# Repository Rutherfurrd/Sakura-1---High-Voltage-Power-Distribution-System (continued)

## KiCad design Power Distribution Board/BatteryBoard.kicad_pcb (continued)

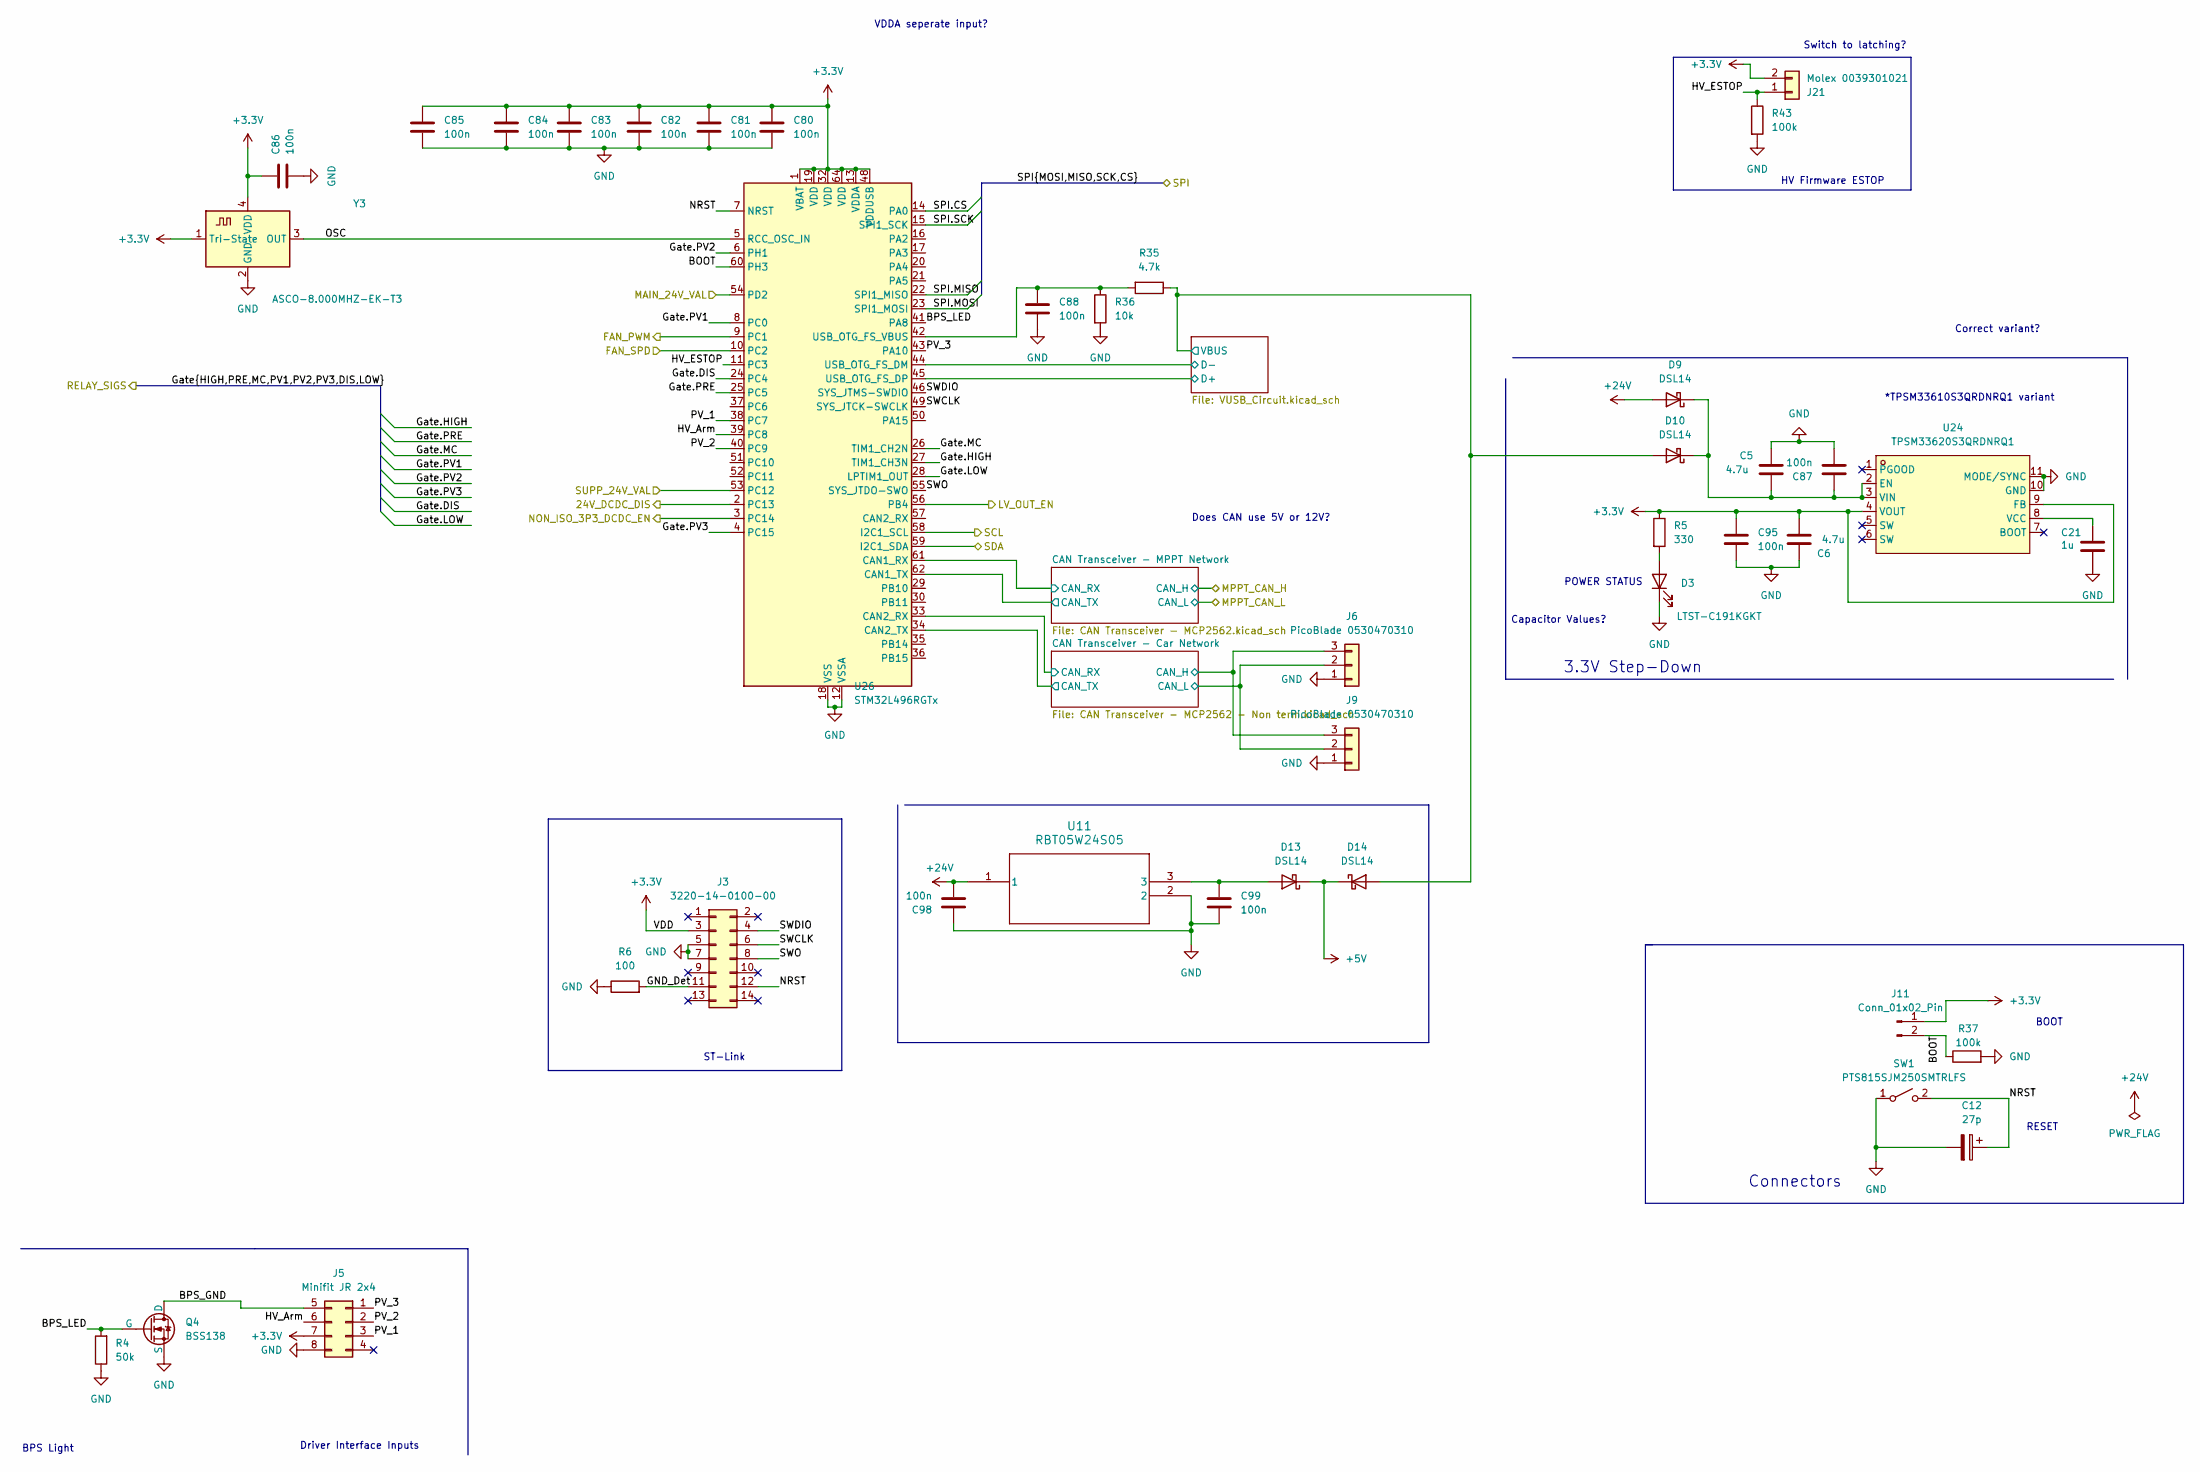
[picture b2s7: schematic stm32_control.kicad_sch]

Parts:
C5, C6: 4.7u; C_0603_1608Metric_Pad1.08x0.95mm_HandSolder; Rating 50V; LCSC C19666
C12: 27p; C_0603_1608Metric_Pad1.08x0.95mm_HandSolder; LCSC C107045
C21: 1u; C_0603_1608Metric_Pad1.08x0.95mm_HandSolder; LCSC C15849
C80, C81, C82, C83, C84, C85, C86, C87, C88, C95, C98, C99: 100n; C_0603_1608Metric_Pad1.08x0.95mm_HandSolder; Rating 50V; LCSC C14663
D3: LTST-C191KGKT; LED_0603_1608Metric_Pad1.05x0.95mm_HandSolder; DigiKey_Part_Number 160-1446-1-ND
D9, D10, D13, D14: DSL14; D_SOD-123FL; LCSC C22466349
J3: 3220-14-0100-00; PinHeader_2x07_P1.27mm_Vertical_SMD; DigiKey_Part_Number SAM13170CT-ND
J5: Minifit JR 2x4; Molex_Mini-Fit_Jr_5566-08A_2x04_P4.20mm_Vertical; DigiKey_Part_Number WM3846-ND
J6, J9: PicoBlade 0530470310; Molex_PicoBlade_53047-0310_1x03_P1.25mm_Vertical; DigiKey_Part_Number WM1732-ND
J11: Conn_01x02_Pin; HARWIN_M20-9990246; DigiKey_Part_Number 952-2262-ND
J21: Molex 0039301021; Molex_Mini-Fit_Jr_5566-02A_2x01_P4.20mm_Vertical; DigiKey_Part_Number WM3843-ND
Q4: BSS138; SOT-23; LCSC C7420339
R4: 50k; R_0603_1608Metric_Pad0.98x0.95mm_HandSolder; LCSC C23184
R5: 330; R_0603_1608Metric_Pad0.98x0.95mm_HandSolder; LCSC C23138
R6: 100; R_0603_1608Metric_Pad0.98x0.95mm_HandSolder; LCSC C22775
R35: 4.7k; R_0603_1608Metric_Pad0.98x0.95mm_HandSolder; LCSC C23162
R36: 10k; R_0603_1608Metric_Pad0.98x0.95mm_HandSolder; LCSC C95204
R37, R43: 100k; R_0603_1608Metric_Pad0.98x0.95mm_HandSolder; LCSC C25803
SW1: PTS815SJM250SMTRLFS; SW_SPST_PTS810; DigiKey_Part_Number CKN12215-2-ND
U11: RBT05W24S05; RBT10W24S05_XPP_XPR; DigiKey_Part_Number 1470-RBT05W24S05-ND
U24: TPSM33620S3QRDNRQ1; QFN-11_L4.5-W3.5-P0.50-TL_TPSM365R6FRDNR; MPN TPSM33620S3QRDNRQ1; LCSC C49261907
U26: STM32L496RGTx; LQFP-64_10x10mm_P0.5mm; LCSC C124720
Y3: ASCO-8.000MHZ-EK-T3; Oscillator_SMD_Abracon_ASCO-4Pin_1.6x1.2mm; DigiKey_Part_Number 535-12077-1-ND

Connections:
+3.3V: C6.1, C80.1, C81.1, C82.1, C83.1, C84.1, C85.1, C86.1, C95.1, J3.3, J5.7, J11.1, J21.2, R5.1, U24.4 (VOUT), U24.9 (FB), U26.1 (VBAT), U26.13 (VDDA), U26.19 (VDD), U26.32 (VDD), U26.48 (VDDUSB), U26.64 (VDD), Y3.1 (Tri-State), Y3.4 (VDD); also elsewhere on the board
+5V: D13.1 (K), D14.1 (K); also elsewhere on the board
+24V: C98.2, D9.2 (A), U11.1; also elsewhere on the board
/24 Supplementary Switch/LV_OUT_EN: U26.56 (PB4); also elsewhere on the board
/24 Supplementary Switch/MAIN_24V_VALID: U26.53 (PC12); also elsewhere on the board
/24 Supplementary Switch/SUPP_24V_VALID: U26.54 (PD2); also elsewhere on the board
/<NO NET>: U26.58 (I2C1_SCL); also elsewhere on the board
/Battery Fan/FAN1_SPD: U26.10 (PC2); also elsewhere on the board
/Battery Fan/FAN_PWM: U26.9 (PC1); also elsewhere on the board
/Gate.DIS: U26.24 (PC4); also elsewhere on the board
/Gate.HIGH: U26.27 (TIM1_CH3N); also elsewhere on the board
/Gate.LOW: U26.28 (LPTIM1_OUT); also elsewhere on the board
/Gate.MC: U26.26 (TIM1_CH2N); also elsewhere on the board
/Gate.PRE: U26.25 (PC5); also elsewhere on the board
/Gate.PV1: U26.8 (PC0); also elsewhere on the board
/Gate.PV2: U26.6 (PH1); also elsewhere on the board
/Gate.PV3: U26.4 (PC15); also elsewhere on the board
/LV Step-down/24V_CONV_EN_ACTIVELOW: U26.2 (PC13); also elsewhere on the board
/LV Step-down/NON_ISO_3P3_EN: U26.3 (PC14); also elsewhere on the board
/SDA: U26.59 (I2C1_SDA); also elsewhere on the board
/SPI.CS: U26.14 (PA0); also elsewhere on the board
/SPI.MISO: U26.22 (SPI1_MISO); also elsewhere on the board
/SPI.MOSI: U26.23 (SPI1_MOSI); also elsewhere on the board
/SPI.SCK: U26.15 (SPI1_SCK); also elsewhere on the board
/STM32_CONTROL/BOOT: J11.2, R37.1, U26.60 (PH3)
/STM32_CONTROL/BPS_GND: J5.5, Q4.1 (D)
/STM32_CONTROL/BPS_LED: Q4.2 (G), R4.2, U26.41 (PA8)
/STM32_CONTROL/CAN Transceiver - Car Network/CAN+: J6.3, J9.3; also elsewhere on the board
/STM32_CONTROL/CAN Transceiver - Car Network/CAN-: J6.2, J9.2; also elsewhere on the board
/STM32_CONTROL/CAN Transceiver - Car Network/CAN_RX: U26.33 (CAN2_RX); also elsewhere on the board
/STM32_CONTROL/CAN Transceiver - Car Network/CAN_TX: U26.34 (CAN2_TX); also elsewhere on the board
/STM32_CONTROL/CAN Transceiver - MPPT Network/CAN_RX: U26.61 (CAN1_RX); also elsewhere on the board
/STM32_CONTROL/CAN Transceiver - MPPT Network/CAN_TX: U26.62 (CAN1_TX); also elsewhere on the board
/STM32_CONTROL/GND_Det: J3.11, R6.2
/STM32_CONTROL/HV_Arm: J5.6, U26.39 (PC8)
/STM32_CONTROL/HV_ESTOP: J21.1, R43.1, U26.11 (PC3)
/STM32_CONTROL/NRST: C12.1, J3.12, SW1.2 (B), U26.7 (NRST)
/STM32_CONTROL/OSC: U26.5 (RCC_OSC_IN), Y3.3 (OUT)
/STM32_CONTROL/PV_1: J5.3, U26.38 (PC7)
/STM32_CONTROL/PV_2: J5.2, U26.40 (PC9)
/STM32_CONTROL/PV_3: J5.1, U26.43 (PA10)
/STM32_CONTROL/SWCLK: J3.6, U26.49 (SYS_JTCK-SWCLK)
/STM32_CONTROL/SWDIO: J3.4, U26.46 (SYS_JTMS-SWDIO)
/STM32_CONTROL/SWO: J3.8, U26.55 (SYS_JTDO-SWO)
/STM32_CONTROL/USC_CIRCUIT/D+: U26.45 (USB_OTG_FS_DP); also elsewhere on the board
/STM32_CONTROL/USC_CIRCUIT/D-: U26.44 (USB_OTG_FS_DM); also elsewhere on the board
/STM32_CONTROL/USC_CIRCUIT/VBUS: D10.2 (A), D14.2 (A), R35.1; also elsewhere on the board
GND: C5.2, C6.2, C12.2, C21.1, C80.2, C81.2, C82.2, C83.2, C84.2, C85.2, C86.2, C87.2, C88.2, C95.2, C98.1, C99.2, D3.1 (K), J3.5, J3.7, J5.8, J6.1, J9.1, Q4.3 (S), R4.1, R6.1, R36.2, R37.2, R43.2, SW1.1 (A), U11.2, U24.10 (GND), U24.11 (MODE/SYNC), U26.12 (VSSA), U26.18 (VSS), U26.31 (VSS), U26.47 (VSS), U26.63 (VSS), Y3.2 (GND); also elsewhere on the board
unnamed: D3.2 (A), R5.2
unnamed: C5.1, C87.1, D9.1 (K), D10.1 (K), U24.2 (EN), U24.3 (VIN)
unnamed: C99.1, D13.2 (A), U11.3
unnamed: C21.2, U24.8 (VCC)
unnamed: C88.1, R35.2, R36.1, U26.42 (USB_OTG_FS_VBUS)

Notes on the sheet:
HV Firmware ESTOP
Does CAN use 5V or 12V?
Capacitor Values?
*TPSM33610S3QRDNRQ1 variant
Driver Interface Inputs
BPS Light
Correct variant?
Connectors
3.3V Step-Down
ST-Link
BOOT
Switch to latching?
RESET
VDDA seperate input?
POWER STATUS

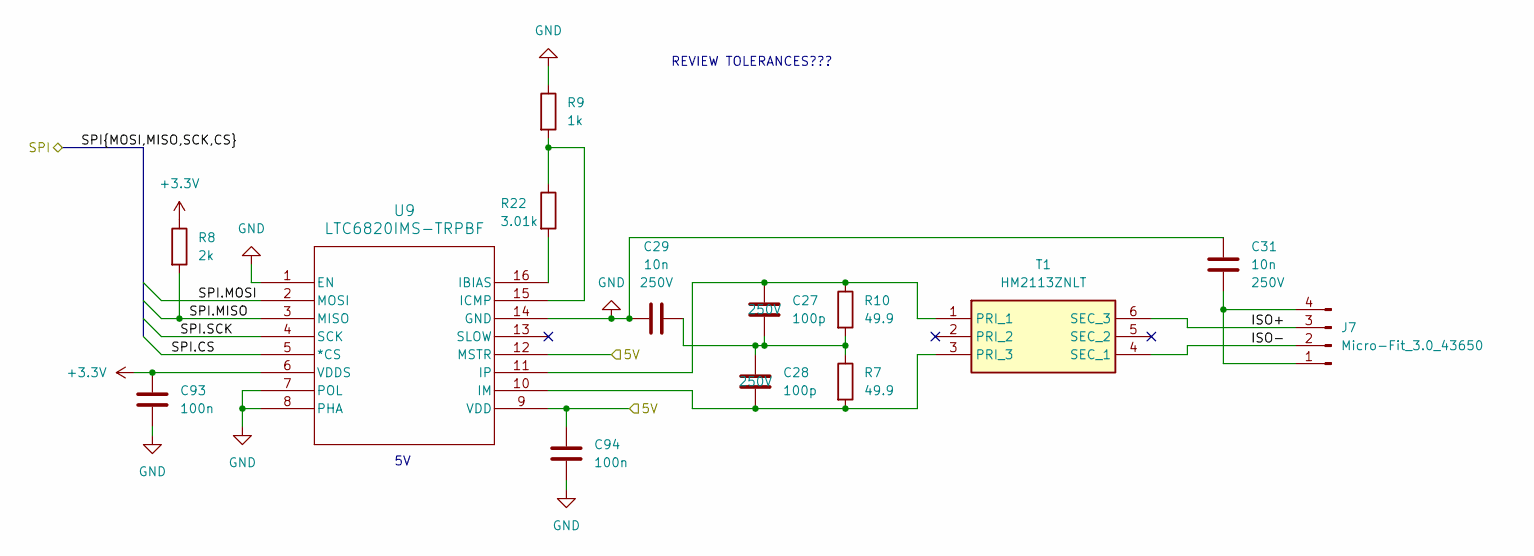
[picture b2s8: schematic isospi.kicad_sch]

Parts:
C27, C28: 100p; C_0603_1608Metric_Pad1.08x0.95mm_HandSolder; LCSC C14858
C29, C31: 10n; C_0603_1608Metric_Pad1.08x0.95mm_HandSolder; LCSC C57112
C93, C94: 100n; C_0603_1608Metric_Pad1.08x0.95mm_HandSolder; Rating 50V; LCSC C14663
J7: Micro-Fit_3.0_43650; Molex_Micro-Fit_3.0_43650-0415_1x04_P3.00mm_Vertical; DigiKey_Part_Number WM1919-ND
R7, R10: 49.9; R_0603_1608Metric_Pad0.98x0.95mm_HandSolder; LCSC C23185
R8: 2k; R_0603_1608Metric_Pad0.98x0.95mm_HandSolder; LCSC C22975
R9: 1k; R_0603_1608Metric_Pad0.98x0.95mm_HandSolder; LCSC C21190
R22: 3.01k; R_0603_1608Metric_Pad0.98x0.95mm_HandSolder; LCSC C22991
T1: HM2113ZNLT; Mouser Part Number 673-HM2113ZNLT
U9: LTC6820IMS-TRPBF; MS_05-08-1669_ADI; LCSC C581009

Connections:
+3.3V: C93.1, R8.1, U9.6 (VDDS); also elsewhere on the board
+5V: C94.1, U9.9 (VDD), U9.12 (MSTR); also elsewhere on the board
/ISOSPI/ISO+: J7.3, T1.6 (SEC_3)
/ISOSPI/ISO-: J7.2, T1.4 (SEC_1)
/SPI.CS: U9.5 (*CS); also elsewhere on the board
/SPI.MISO: R8.2, U9.3 (MISO); also elsewhere on the board
/SPI.MOSI: U9.2 (MOSI); also elsewhere on the board
/SPI.SCK: U9.4 (SCK); also elsewhere on the board
GND: C29.1, C31.2, C93.2, C94.2, R9.1, U9.1 (EN), U9.7 (POL), U9.8 (PHA), U9.14 (GND); also elsewhere on the board
unnamed: C27.2, C28.1, C29.2, R7.1, R10.2
unnamed: C31.1, J7.1, J7.4
unnamed: C27.1, R10.1, T1.1 (PRI_1), U9.11 (IP)
unnamed: C28.2, R7.2, T1.3 (PRI_3), U9.10 (IM)
unnamed: R22.2, U9.16 (IBIAS)
unnamed: R9.2, R22.1, U9.15 (ICMP)

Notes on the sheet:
REVIEW TOLERANCES???

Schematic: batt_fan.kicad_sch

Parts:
C48: 10u; CP_Radial_D10.0mm_P5.00mm; DigiKey_Part_Number 450BXC10MEFC10X20
J8: B4B-PH-K-S; JST_PH_B4B-PH-K_1x04_P2.00mm_Vertical; DigiKey_Part_Number N/A
Q14: BSS138; SOT-23; LCSC C7420339
R19, R41: 2k; R_0603_1608Metric_Pad0.98x0.95mm_HandSolder; LCSC C22975

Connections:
+3.3V: R19.1, R41.1; also elsewhere on the board
+24V: C48.1, J8.3; also elsewhere on the board
/Battery Fan/FAN1_SPD: J8.1, R19.2; also elsewhere on the board
/Battery Fan/FAN_PWM: Q14.1 (G), R41.2; also elsewhere on the board
GND: C48.2, J8.2, Q14.2 (S); also elsewhere on the board
unnamed: J8.4, Q14.3 (D)

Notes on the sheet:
PWR, GND, SENSOR, CNTRL
24 kHz
24VDC, 12W per fan

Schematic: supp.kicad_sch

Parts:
C14: 220u; CP_Radial_D10.0mm_P5.00mm; DigiKey_Part_Number CAP ALUM 220UF 20% 50V RADIAL TH
C38: 1n; C_0603_1608Metric_Pad1.08x0.95mm_HandSolder; LCSC C1588
C64, C65, C75: 10u; C_1206_3216Metric_Pad1.33x1.80mm_HandSolder; LCSC C13585
C74, C76, C77, C78, C79: 100n; C_0603_1608Metric_Pad1.08x0.95mm_HandSolder; Rating 50V; LCSC C14663
D15, D16: SMF30A; D_SMF; LCSC C19077518
J15, J25: Molex 0039301021; Molex_Mini-Fit_Jr_5566-02A_2x01_P4.20mm_Vertical; DigiKey_Part_Number WM3843-ND
K4, K5: G5Q-1A-EU DC24; Relay_SPST_Omron-G5Q-1A; Rating Z5361-ND
Q7, Q8: SI4909DY-T1-GE3; SOIC_09DY-T1-GE3_VIS; LCSC C222523
Q15: BSS138; SOT-23; LCSC C7420339
R26, R27: 100k; R_0603_1608Metric_Pad0.98x0.95mm_HandSolder; LCSC C25803
R28: 15k; R_0603_1608Metric_Pad0.98x0.95mm_HandSolder; LCSC C22809
R32: 2k; R_0603_1608Metric_Pad0.98x0.95mm_HandSolder; LCSC C22975
R45: 120k; R_0603_1608Metric_Pad0.98x0.95mm_HandSolder; LCSC C25808
R46, R61, R62, R63: 2M; R_0603_1608Metric_Pad0.98x0.95mm_HandSolder; LCSC C22976
R47, R64: 75k; R_0603_1608Metric_Pad0.98x0.95mm_HandSolder; LCSC C23242
R49: 255k; R_0805_2012Metric_Pad1.20x1.40mm_HandSolder; LCSC C17578
R51, R53: 20k; R_0603_1608Metric_Pad0.98x0.95mm_HandSolder; LCSC C4184
U3: R-7812-0.5; Converter_DCDC_RECOM_R-78E-0.5_THT; DigiKey_Part_Number 945-1032-ND
U6: LTC4418CUF-TRPBF; UF_20_ADI; LCSC C688512

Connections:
+3.3V: R51.1, R53.1; also elsewhere on the board
+24V: C76.2, K4.3, K5.1, K5.2, U3.1 (IN); also elsewhere on the board
/24 Supplementary Switch/12V_CAN: C74.2, U3.3 (OUT); also elsewhere on the board
/24 Supplementary Switch/24V_MAIN: C64.1, Q7.5 (D2), Q7.6 (D2), R46.1, R61.1, U6.17 (V1); also elsewhere on the board
/24 Supplementary Switch/24V_SUPP: C75.1, Q8.5 (D2), Q8.6 (D2), R62.1, R63.1, U6.16 (V2); also elsewhere on the board
/24 Supplementary Switch/24_OUT: K5.3; also elsewhere on the board
/24 Supplementary Switch/LV_OUT_EN: Q15.1 (G), R27.1; also elsewhere on the board
/24 Supplementary Switch/MAIN_24V_VALID: R51.2, U6.6 (*VALID1); also elsewhere on the board
/24 Supplementary Switch/SUPP_24V_VALID: R53.2, U6.7 (*VALID2); also elsewhere on the board
GND: C14.2, C38.2, C64.2, C65.2, C74.1, C75.2, C76.1, C77.1, C78.1, C79.2, D15.2 (A2), D16.2 (A2), J15.1, J25.1, Q15.2 (S), R27.2, R32.2, R45.2, R47.2, R49.2, R64.2, U3.2 (GND), U6.8 (GND), U6.21 (GND); also elsewhere on the board
unnamed: D15.1 (A1), J15.2, K4.5
unnamed: D16.1 (A1), K5.5, Q15.3 (D)
unnamed: C14.1, C65.1, J25.2, K4.1, K4.2, Q7.7 (D1), Q7.8 (D1), Q8.7 (D1), Q8.8 (D1), U6.15 (VOUT)
unnamed: Q7.2 (G1), Q7.4 (G2), U6.13 (G1)
unnamed: C77.2, Q7.1 (S1), Q7.3 (S2), U6.14 (VS1)
unnamed: Q8.2 (G1), Q8.4 (G2), U6.11 (G2)
unnamed: C78.2, Q8.1 (S1), Q8.3 (S2), U6.12 (VS2)
unnamed: R26.2, R28.1
unnamed: R28.2, R32.1
unnamed: C79.1, U6.10 (INTVCC), U6.18 (EN), U6.19 (*SHDN)
unnamed: R49.1, U6.20 (HYS)
unnamed: R46.2, R47.1, U6.3 (OV1)
unnamed: R62.2, R64.1, U6.5 (OV2)
unnamed: C38.1, U6.1 (TMR)
unnamed: R45.1, R61.2, U6.2 (UV1)
unnamed: R26.1, R63.2, U6.4 (UV2)

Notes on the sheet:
17.5V Min
28V Max
Internal 24V Bus
LV ESTOP
24V Nom
500mV Hys
18.1V Min
Test Power, switching bypass

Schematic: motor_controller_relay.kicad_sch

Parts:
C3: C_Polarized
K3: P126CDA; DigiKey_Part_Number 3596-P126CDA-ND
R3: R

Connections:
+24V: K3.3; also elsewhere on the board
/MC Relay/RELAY_IN: C3.2, K3.2; also elsewhere on the board
/MC Relay/RELAY_OUT: K3.1, R3.1; also elsewhere on the board
/MC Relay/RELAY_PROTECTION_CIRCUIT/COIL_NEG: K3.4; also elsewhere on the board
unnamed: C3.1, R3.2

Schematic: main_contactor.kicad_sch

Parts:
C1: C_Polarized
K1: P126CDA; DigiKey_Part_Number 3596-P126CDA-ND
R1: R

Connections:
+24V: K1.3; also elsewhere on the board
/HV_BUS_POS: K1.1; also elsewhere on the board
/Main Contactor High/RELAY_IN: K1.2; also elsewhere on the board
/Main Contactor High/RELAY_PROTECTION_CIRCUIT/COIL_NEG: K1.4; also elsewhere on the board
unnamed: C1.1, R1.2

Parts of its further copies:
K2: P126CDA; DigiKey_Part_Number 3596-P126CDA-ND

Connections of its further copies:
+24V: K2.3; also elsewhere on the board
-BATT: K2.1; also elsewhere on the board
/Main Contactor Low/RELAY_IN: K2.2; also elsewhere on the board
/Main Contactor Low/RELAY_PROTECTION_CIRCUIT/COIL_NEG: K2.4; also elsewhere on the board

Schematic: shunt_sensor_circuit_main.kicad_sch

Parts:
C39: 10n; C_0603_1608Metric_Pad1.08x0.95mm_HandSolder; Rating 50V; LCSC C57112
C43, C45, C53: 100n; C_0603_1608Metric_Pad1.08x0.95mm_HandSolder; Rating 50V; LCSC C14663
R67: 0.5m; RES-TH_HOFLQ60-100A-50MV-7H27; Rating 200V; LCSC C508587
R78, R79: 100; R_0603_1608Metric_Pad0.98x0.95mm_HandSolder; Rating 75V; LCSC C22775
U42: AMC1302DWVR; DWV0008A; LCSC C2863209
U43: MCP3425A0T-E/CH; SOT-23-6; LCSC C66823

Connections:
+3.3V: C45.1, C53.1, U42.8 (VDD2), U43.5 (V_{DD}); also elsewhere on the board
+3.3VP: C43.2, U42.1 (VDD1); also elsewhere on the board
/<NO NET>: U43.3 (SCL); also elsewhere on the board
/HV_BUS_NEG: C39.2, R67.1, U42.3 (VINN); also elsewhere on the board
/Main Contactor Low/RELAY_IN: C39.1, C43.1, R67.2, U42.2 (VINP), U42.4 (GND1); also elsewhere on the board
/SDA: U43.4 (SDA); also elsewhere on the board
GND: C45.2, C53.2, U42.5 (GND2), U43.2 (V_{SS}); also elsewhere on the board
unnamed: R79.1, U42.6 (VOUTN)
unnamed: R78.1, U42.7 (VOUTP)
unnamed: R79.2, U43.1 (Vin+)
unnamed: R78.2, U43.6 (Vin-)

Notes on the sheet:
Overspec?
40A
*R 10K, 100KHZ. 2K, 400KHZ.
Choose R to fit within bounds of ADC
+- 50 mV

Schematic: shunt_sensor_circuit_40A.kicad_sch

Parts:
C34: 10n; C_0603_1608Metric_Pad1.08x0.95mm_HandSolder; Rating 50V; LCSC C57112
C42, C44, C51: 100n; C_0603_1608Metric_Pad1.08x0.95mm_HandSolder; Rating 50V; LCSC C14663
R48: 0.5m; RES-TH_HOFLQ60-100A-50MV-7H27; Rating 200V; LCSC C508587
R72, R73: 100; R_0603_1608Metric_Pad0.98x0.95mm_HandSolder; Rating 75V; LCSC C22775
U36: AMC1302DWVR; DWV0008A; LCSC C2863209
U37: MCP3425A1T-E/CH; SOT-23-6; LCSC C625479

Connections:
+3.3V: C44.1, C51.1, U36.8 (VDD2), U37.5 (V_{DD}); also elsewhere on the board
+3.3VP: C42.2, U36.1 (VDD1); also elsewhere on the board
/<NO NET>: U37.3 (SCL); also elsewhere on the board
/HV_BUS_NEG: C34.1, C42.1, R48.2, U36.2 (VINP), U36.4 (GND1); also elsewhere on the board
/MC Current Sense/SHUNT_Supply: C34.2, R48.1, U36.3 (VINN); also elsewhere on the board
/SDA: U37.4 (SDA); also elsewhere on the board
GND: C44.2, C51.2, U36.5 (GND2), U37.2 (V_{SS}); also elsewhere on the board
unnamed: R73.1, U36.6 (VOUTN)
unnamed: R72.1, U36.7 (VOUTP)
unnamed: R73.2, U37.1 (Vin+)
unnamed: R72.2, U37.6 (Vin-)

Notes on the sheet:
Overspec?
40A
*R 10K, 100KHZ. 2K, 400KHZ.
Choose R to fit within bounds of ADC
+- 50 mV

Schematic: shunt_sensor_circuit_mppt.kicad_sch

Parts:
C66: 10n; C_0603_1608Metric_Pad1.08x0.95mm_HandSolder; Rating 50V; LCSC C57112
C67, C68, C69: 100n; C_0603_1608Metric_Pad1.08x0.95mm_HandSolder; Rating 50V; LCSC C14663
R50: 0.5m; RES-TH_HOFLQ60-100A-50MV-7H27; Rating 200V; LCSC C508587
R74, R75: 100; R_0603_1608Metric_Pad0.98x0.95mm_HandSolder; Rating 75V; LCSC C22775
U38: AMC1302DWVR; DWV0008A; LCSC C2863209
U39: MCP3425A2T-E/CH; SOT-23-6; LCSC C625480

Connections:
+3.3V: C68.1, C69.1, U38.8 (VDD2), U39.5 (V_{DD}); also elsewhere on the board
+3.3VP: C67.2, U38.1 (VDD1); also elsewhere on the board
/<NO NET>: U39.3 (SCL); also elsewhere on the board
/Elmar Racing MPPTS/HV_BUS_NEG: C66.2, R50.1, U38.3 (VINN); also elsewhere on the board
/HV_BUS_NEG: C66.1, C67.1, R50.2, U38.2 (VINP), U38.4 (GND1); also elsewhere on the board
/SDA: U39.4 (SDA); also elsewhere on the board
GND: C68.2, C69.2, U38.5 (GND2), U39.2 (V_{SS}); also elsewhere on the board
unnamed: R75.1, U38.6 (VOUTN)
unnamed: R74.1, U38.7 (VOUTP)
unnamed: R75.2, U39.1 (Vin+)
unnamed: R74.2, U39.6 (Vin-)

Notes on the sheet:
40A
*R 10K, 100KHZ. 2K, 400KHZ.
+- 50 mV

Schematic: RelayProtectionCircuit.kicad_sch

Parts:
D22: SMF30A; D_SMF; LCSC C19077518
Q1: BSS138; SOT-23; LCSC C7420339
R55: 50k; R_0603_1608Metric_Pad0.98x0.95mm_HandSolder; LCSC C23184

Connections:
/Elmar Racing MPPTS/COIL_RET_1: D22.1 (A1), Q1.3 (D); also elsewhere on the board
/Gate.PV1: Q1.1 (G), R55.1; also elsewhere on the board
GND: D22.2 (A2), Q1.2 (S), R55.2; also elsewhere on the board

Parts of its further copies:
D1, D5, D6, D27, D28, D29, D30: SMF30A; D_SMF; LCSC C19077518
Q2, Q3, Q9, Q10, Q11, Q12, Q13: BSS138; SOT-23; LCSC C7420339
R24, R33, R42, R56, R59, R60, R68: 50k; R_0603_1608Metric_Pad0.98x0.95mm_HandSolder; LCSC C23184

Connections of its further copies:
/Elmar Racing MPPTS/COIL_RET_2: D27.1 (A1), Q2.3 (D); also elsewhere on the board
/Elmar Racing MPPTS/COIL_RET_3: D28.1 (A1), Q3.3 (D); also elsewhere on the board
/Gate.DIS: Q12.1 (G), R68.1; also elsewhere on the board
/Gate.HIGH: Q9.1 (G), R24.1; also elsewhere on the board
/Gate.LOW: Q10.1 (G), R33.1; also elsewhere on the board
/Gate.MC: Q13.1 (G), R42.1; also elsewhere on the board
/Gate.PRE: Q11.1 (G), R60.1; also elsewhere on the board
/Gate.PV2: Q2.1 (G), R56.1; also elsewhere on the board
/Gate.PV3: Q3.1 (G), R59.1; also elsewhere on the board
/MC Relay/RELAY_PROTECTION_CIRCUIT/COIL_NEG: D6.1 (A1), Q13.3 (D); also elsewhere on the board
/Main Contactor High/RELAY_PROTECTION_CIRCUIT/COIL_NEG: D1.1 (A1), Q9.3 (D); also elsewhere on the board
/Main Contactor Low/RELAY_PROTECTION_CIRCUIT/COIL_NEG: D5.1 (A1), Q10.3 (D); also elsewhere on the board
/Pre & Dis Charge/RELAY_PROTECTION_CIRCUIT1/COIL_NEG: D30.1 (A1), Q12.3 (D); also elsewhere on the board
/Pre & Dis Charge/RELAY_PROTECTION_CIRCUIT/COIL_NEG: D29.1 (A1), Q11.3 (D); also elsewhere on the board
GND: D1.2 (A2), D5.2 (A2), D6.2 (A2), D27.2 (A2), D28.2 (A2), D29.2 (A2), D30.2 (A2), Q2.2 (S), Q3.2 (S), Q9.2 (S), Q10.2 (S), Q11.2 (S), Q12.2 (S), Q13.2 (S), R24.2, R33.2, R42.2, R56.2, R59.2, R60.2, R68.2; also elsewhere on the board

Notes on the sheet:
Rev 30V Clamp 48V

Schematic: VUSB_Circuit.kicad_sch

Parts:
J4: USB_C_Receptacle_USB2.0_16P; USB_C_Receptacle_HRO_TYPE-C-31-M-12; DigiKey_Part_Number 2223-UJ20-C-H-G-SMT-1-P16-TRCT-ND
R21, R23: 5.1k; R_0603_1608Metric_Pad0.98x0.95mm_HandSolder; LCSC C23186
R31, R65: 22; R_0603_1608Metric_Pad0.98x0.95mm_HandSolder; LCSC C23345
U23: SRV05-4; SOT-23-6; LCSC C85364

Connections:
+3.3V: U23.5 (VP); also elsewhere on the board
/STM32_CONTROL/USC_CIRCUIT/D+: R65.2, U23.3 (IO2); also elsewhere on the board
/STM32_CONTROL/USC_CIRCUIT/D-: R31.2, U23.1 (IO1); also elsewhere on the board
/STM32_CONTROL/USC_CIRCUIT/VBUS: J4.A4 (VBUS), J4.A9 (VBUS), J4.B4 (VBUS), J4.B9 (VBUS); also elsewhere on the board
GND: J4.A1 (GND), J4.A12 (GND), J4.B1 (GND), J4.B12 (GND), J4.SH (SHIELD), R21.2, R23.2, U23.2 (VN); also elsewhere on the board
unnamed: J4.A5 (CC1), R21.1
unnamed: J4.B5 (CC2), R23.1
unnamed: J4.A6 (D+), J4.B6 (D+), R65.1
unnamed: J4.A7 (D-), J4.B7 (D-), R31.1

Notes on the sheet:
USB Programming

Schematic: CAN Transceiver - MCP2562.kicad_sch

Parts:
C13, C15: 100p; C_0402_1005Metric_Pad0.74x0.62mm_HandSolder; LCSC C1546
C89, C91, C96: 100n; C_0603_1608Metric_Pad1.08x0.95mm_HandSolder; Rating 50V; LCSC C14663
D4, D11: H5VND5BA; D_SOD-523; LCSC C42413899
R11, R13: 60; R_0402_1005Metric_Pad0.72x0.64mm_HandSolder; LCSC C60310
U33: MCP2562-E-SN; SOIC-8_3.9x4.9mm_P1.27mm; LCSC C124016
U34: ACT1210-510-2P-TL00; CHOKE_10-2P-TL00_TDK; LCSC C95572

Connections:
+3.3V: C91.1, U33.5 (Vio); also elsewhere on the board
+5V: C89.2, U33.3 (VDD); also elsewhere on the board
/CAN+: U34.4; also elsewhere on the board
/CAN-: U34.3; also elsewhere on the board
/STM32_CONTROL/CAN Transceiver - MPPT Network/CAN_RX: U33.4 (RXD); also elsewhere on the board
/STM32_CONTROL/CAN Transceiver - MPPT Network/CAN_TX: U33.1 (TXD); also elsewhere on the board
GND: C13.1, C15.2, C89.1, C91.2, C96.2, D4.2 (A2), D11.2 (A2), U33.2 (VSS), U33.8 (STBY); also elsewhere on the board
unnamed: C96.1, R11.2, R13.1
unnamed: C15.1, D4.1 (A1), R13.2, U33.6 (CANL), U34.2
unnamed: C13.2, D11.1 (A1), R11.1, U33.7 (CANH), U34.1

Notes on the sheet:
CAN Tranciever
Terminating?

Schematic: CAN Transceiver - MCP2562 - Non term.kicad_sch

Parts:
C11, C16: 100p; C_0402_1005Metric_Pad0.74x0.62mm_HandSolder; LCSC C1546
C90, C92: 100n; C_0603_1608Metric_Pad1.08x0.95mm_HandSolder; Rating 50V; LCSC C14663
D8, D12: H5VND5BA; D_SOD-523; LCSC C42413899
U22: MCP2562-E-SN; SOIC-8_3.9x4.9mm_P1.27mm; LCSC C124016
U25: ACT1210-510-2P-TL00; CHOKE_10-2P-TL00_TDK; LCSC C95572

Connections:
+3.3V: C92.1, U22.5 (Vio); also elsewhere on the board
+5V: C90.2, U22.3 (VDD); also elsewhere on the board
/STM32_CONTROL/CAN Transceiver - Car Network/CAN+: U25.4; also elsewhere on the board
/STM32_CONTROL/CAN Transceiver - Car Network/CAN-: U25.3; also elsewhere on the board
/STM32_CONTROL/CAN Transceiver - Car Network/CAN_RX: U22.4 (RXD); also elsewhere on the board
/STM32_CONTROL/CAN Transceiver - Car Network/CAN_TX: U22.1 (TXD); also elsewhere on the board
GND: C11.1, C16.2, C90.1, C92.2, D8.2 (A2), D12.2 (A2), U22.2 (VSS), U22.8 (STBY); also elsewhere on the board
unnamed: C16.1, D8.1 (A1), U22.6 (CANL), U25.2
unnamed: C11.2, D12.1 (A1), U22.7 (CANH), U25.1

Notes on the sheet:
CAN Tranciever
Terminating?

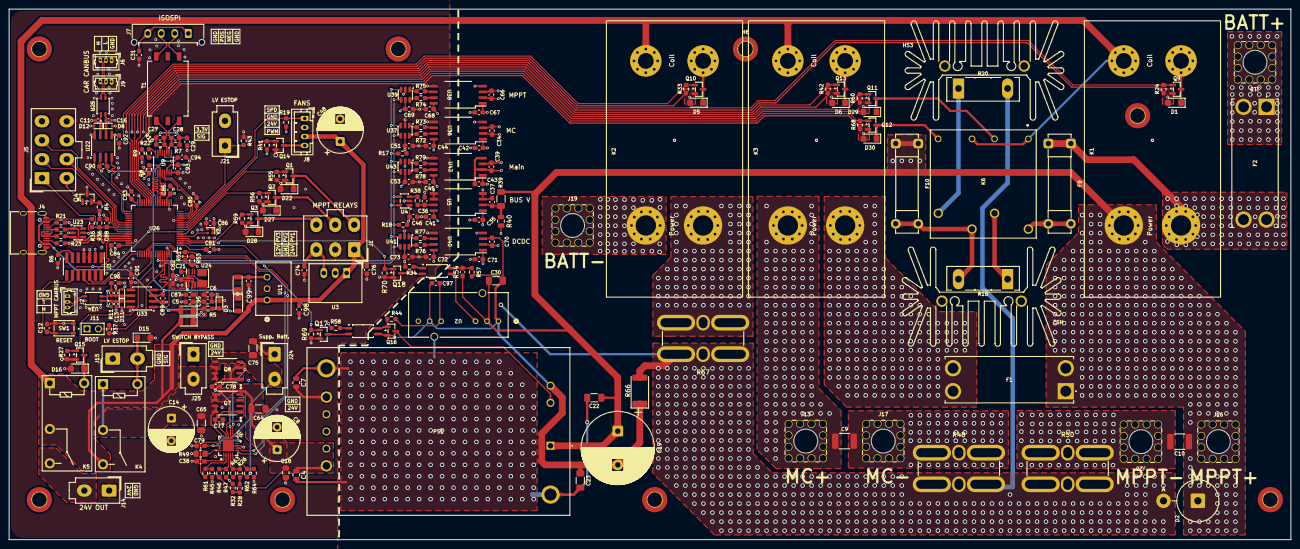
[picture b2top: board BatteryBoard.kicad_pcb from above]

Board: 4 copper layers, 284.3 x 117.7 mm, 247 parts (0 on the bottom side), 145 nets.

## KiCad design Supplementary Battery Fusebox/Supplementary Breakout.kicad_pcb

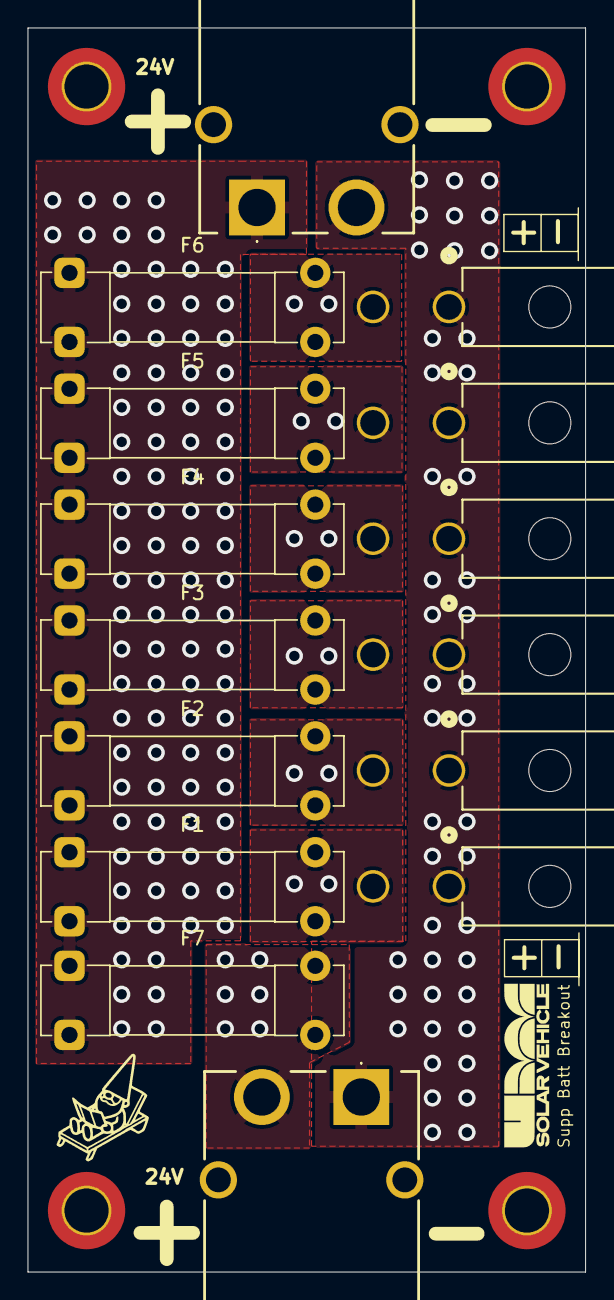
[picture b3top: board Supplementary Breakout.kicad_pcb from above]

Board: 2 copper layers, 40.4 x 90.1 mm, 19 parts (0 on the bottom side), 9 nets, no tracks yet.

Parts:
F1, F2, F3, F4, F5, F6, F7: 3568 Holder; Fuseholder_Clip-5x20mm_Bel_FC-203-22_Lateral_P17.80x5.00mm_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
H1, H2, H3, H4: MountingHole_Pad; MountingHole_3.2mm_M3_DIN965_Pad_TopBottom
J1, J7: XT60; XT60PWM
J8, J9, J10, J11, J12, J13: Molex 5569; CONN_5569-02A_MOL

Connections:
/Supp+: F1.1, F2.1, F3.1, F4.1, F5.1, F6.1, F7.1, J1.1
/Supp-: J1.2, J7.1, J8.1, J9.1, J10.1, J11.1, J12.1, J13.1
unnamed: F7.2, J7.2
unnamed: F1.2, J8.2
unnamed: F2.2, J9.2
unnamed: F3.2, J10.2
unnamed: F4.2, J11.2
unnamed: F5.2, J12.2
unnamed: F6.2, J13.2

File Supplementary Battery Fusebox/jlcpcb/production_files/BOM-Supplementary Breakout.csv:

Comment,Designator,Footprint,LCSC,Quantity
3568 Holder,F4,Fuseholder_Clip-5x20mm_Bel_FC-203-22_Lateral_P17.80x5.00mm_D1.17mm_Horizontal,,1
Molex 5569,J8,CONN_5569-02A_MOL,,1
3568 Holder,F5,Fuseholder_Clip-5x20mm_Bel_FC-203-22_Lateral_P17.80x5.00mm_D1.17mm_Horizontal,,1
XT60,J1,XT60PWM,,1
3568 Holder,F6,Fuseholder_Clip-5x20mm_Bel_FC-203-22_Lateral_P17.80x5.00mm_D1.17mm_Horizontal,,1
3568 Holder,F3,Fuseholder_Clip-5x20mm_Bel_FC-203-22_Lateral_P17.80x5.00mm_D1.17mm_Horizontal,,1
Molex 5569,J9,CONN_5569-02A_MOL,,1
3568 Holder,F1,Fuseholder_Clip-5x20mm_Bel_FC-203-22_Lateral_P17.80x5.00mm_D1.17mm_Horizontal,,1
3568 Holder,F7,Fuseholder_Clip-5x20mm_Bel_FC-203-22_Lateral_P17.80x5.00mm_D1.17mm_Horizontal,,1
XT60,J7,XT60PWM,,1
Molex 5569,J10,CONN_5569-02A_MOL,,1
Molex 5569,J12,CONN_5569-02A_MOL,,1
Molex 5569,J13,CONN_5569-02A_MOL,,1
Molex 5569,J11,CONN_5569-02A_MOL,,1
3568 Holder,F2,Fuseholder_Clip-5x20mm_Bel_FC-203-22_Lateral_P17.80x5.00mm_D1.17mm_Horizontal,,1
